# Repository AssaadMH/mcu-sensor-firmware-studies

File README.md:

# Microcontroller & Sensor Firmware Studies
> A set of small but complete embedded programs — PIC instrumentation with LCD readout, and an NFC tag reader.
`2025` · `PIC` · `mikroC` · `Arduino` · `PN532 NFC` · `HD44780 LCD` · `ADC` · `I2C`

## About

A collection of the smaller embedded programs that make up the everyday practice behind the larger builds — each one complete, compiled and doing a real job on real silicon.

**PIC instrumentation (mikroC).** A digital tachometer that reads three analog channels through the ADC and drives a 16×2 HD44780 LCD in 4-bit mode; and a motor-speed program that computes RPM and voltage and switches a transistor output while displaying the reading. Both carry their full toolchain output — compiled hex, listing and assembly.

**NFC reader.** An Arduino program driving a PN532 module over I2C to read passive MIFARE / ISO 14443A tag UIDs and report them over serial — the access-control front end from an internship task.

None of these is a headline project, but together they are the reason the headline projects work: the LCD, ADC, I2C and serial groundwork that a bigger robot quietly depends on.

## Contents

```
captures/
docs/
kicad/
```

## Notes

## Third-party work used here

Everything in this repository is my own work. It builds on the following, which are **not** mine and are used under their own licences:

- **KiCad** by KiCad project — <https://kicad.org>
- **Proteus Design Suite** by Labcenter Electronics — <https://labcenter.com>

## Author

Lassaad Mahmoudi — <assaadmahmoudi0@gmail.com>  
https://linkedin.com/in/mahmoudi-assaad

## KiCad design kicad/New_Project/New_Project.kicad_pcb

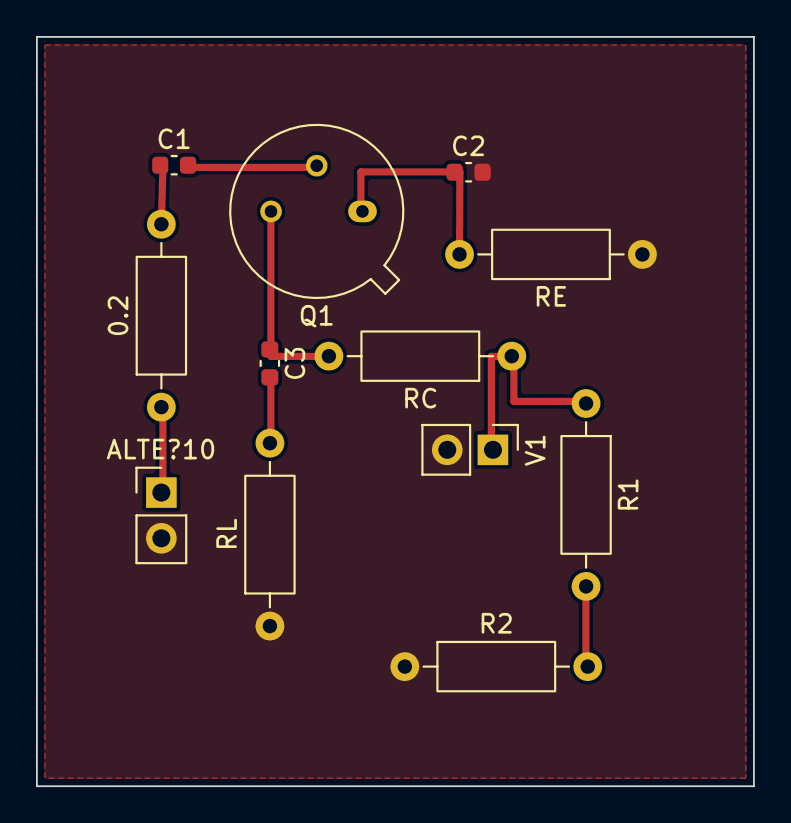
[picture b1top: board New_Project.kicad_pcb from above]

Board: 2 copper layers, 39.8 x 41.6 mm, 12 parts (0 on the bottom side), 9 nets.

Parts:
0.2: RES; R_Axial_DIN0207_L6.3mm_D2.5mm_P10.16mm_Horizontal
ALTE?10: ALTERNATOR; PinHeader_1x02_P2.54mm_Vertical
C1, C3: 100000000pF; C_0603_1608Metric
C2: 220000000; C_0603_1608Metric
Q1: 2N1711; TO-5-3
R1: 180k; R_Axial_DIN0207_L6.3mm_D2.5mm_P10.16mm_Horizontal
R2: 15k; R_Axial_DIN0207_L6.3mm_D2.5mm_P10.16mm_Horizontal
RC: RES; R_Axial_DIN0207_L6.3mm_D2.5mm_P10.16mm_Horizontal
RE: RES; R_Axial_DIN0207_L6.3mm_D2.5mm_P10.16mm_Horizontal
RL: RES; R_Axial_DIN0207_L6.3mm_D2.5mm_P10.16mm_Horizontal
V1: VSOURCE; PinHeader_1x02_P2.54mm_Vertical

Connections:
GND: ALTE?10.2, C2.2, R2.1, RE.1, RL.1, V1.2
N002: C2.1, Q1.1, RE.2
N003: C3.1, Q1.3, RC.2
N004: R1.1, RC.1, V1.1
N005: C1.2, Q1.2
N006: R1.2, R2.2
N007: C3.2, RL.2
N008: 0.2.1, ALTE?10.1
N009: 0.2.2, C1.1

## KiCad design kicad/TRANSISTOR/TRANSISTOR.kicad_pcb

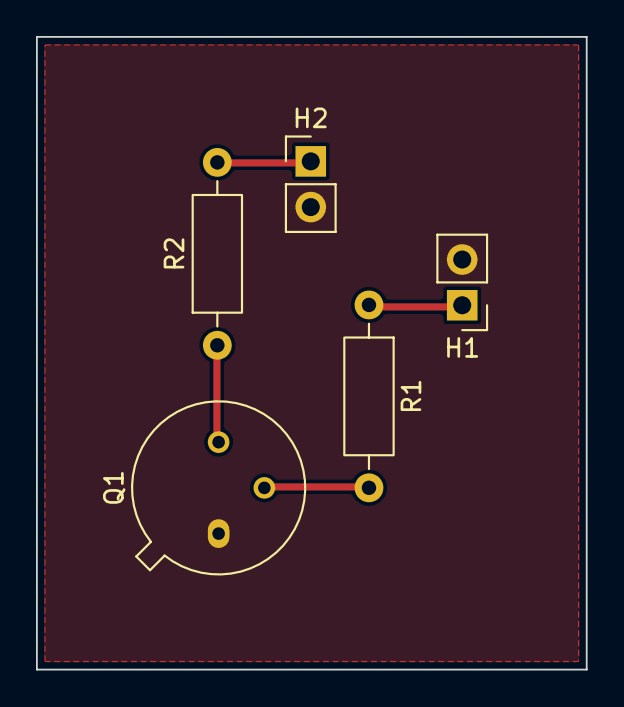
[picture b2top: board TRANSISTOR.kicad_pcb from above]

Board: 2 copper layers, 30.5 x 35.2 mm, 5 parts (0 on the bottom side), 5 nets.

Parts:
H1: 5V; PinHeader_1x02_P2.54mm_Vertical
H2: 1.0; PinHeader_1x02_P2.54mm_Vertical
Q1: 2N1711; TO-5-3
R1: 10k; R_Axial_DIN0207_L6.3mm_D2.5mm_P10.16mm_Horizontal
R2: 100; R_Axial_DIN0207_L6.3mm_D2.5mm_P10.16mm_Horizontal

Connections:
GND: H1.2, H2.2, Q1.1
N002: Q1.2, R1.2
N003: Q1.3, R2.1
N004: H1.1, R1.1
N005: H2.1, R2.2

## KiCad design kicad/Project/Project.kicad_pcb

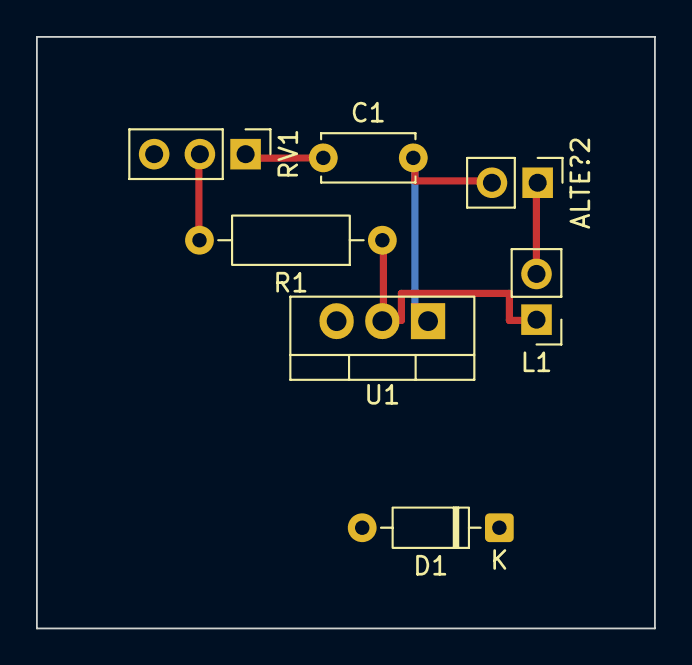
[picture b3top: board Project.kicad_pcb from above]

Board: 2 copper layers, 34.3 x 32.9 mm, 7 parts (0 on the bottom side), 5 nets.

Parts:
ALTE?2: ALTERNATOR; PinHeader_1x02_P2.54mm_Vertical
C1: 400nF; C_Disc_D5.0mm_W2.5mm_P5.00mm
D1: DB3; D_DO-35_SOD27_P7.62mm_Horizontal
L1: 230V; PinHeader_1x02_P2.54mm_Vertical
R1: 10K; R_Axial_DIN0207_L6.3mm_D2.5mm_P10.16mm_Horizontal
RV1: 10K; PinHeader_1x03_P2.54mm_Vertical
U1: BTA16-600C; TO-220-3_Vertical

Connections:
N001: L1.1, R1.1, U1.2
N002: C1.1, RV1.1
N003: ALTE?2.1, L1.2
N004: ALTE?2.2, C1.2, U1.1
N005: R1.2, RV1.2

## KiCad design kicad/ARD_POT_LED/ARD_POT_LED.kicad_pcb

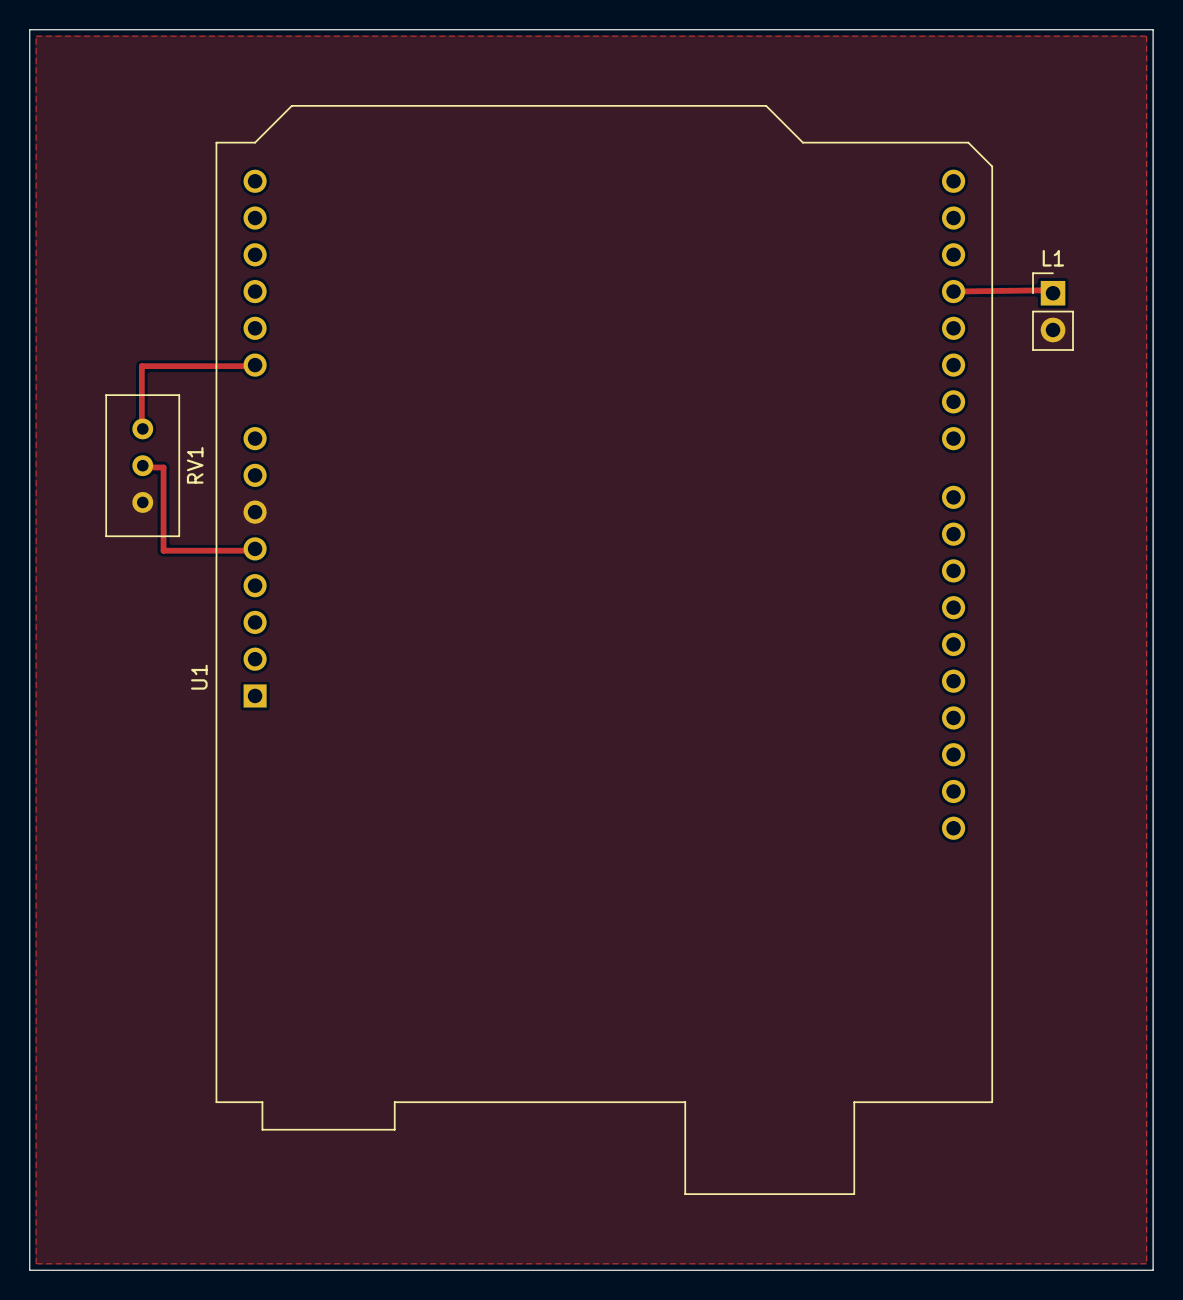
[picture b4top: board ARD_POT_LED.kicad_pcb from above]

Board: 2 copper layers, 77.6 x 85.7 mm, 3 parts (0 on the bottom side), 4 nets.

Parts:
L1: 5V; PinHeader_1x02_P2.54mm_Vertical
RV1: POT; Potentiometer_Bourns_3296W_Vertical
U1: ARDUINO UNO; Arduino_UNO_R3

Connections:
GND: L1.2, RV1.1, U1.6
N002: L1.1, U1.18
N003: RV1.3, U1.9
N004: RV1.2, U1.5
